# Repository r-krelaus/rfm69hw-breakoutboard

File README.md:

# rfm69hw-breakoutboard
KiCAD files for a SMD breakout board for the HopeRF transceiver module RFM69H/RFM69HW.
Needed this for a project to connect the 3.3 V RF module to 5 V Arduino.
Tested it and it works well.

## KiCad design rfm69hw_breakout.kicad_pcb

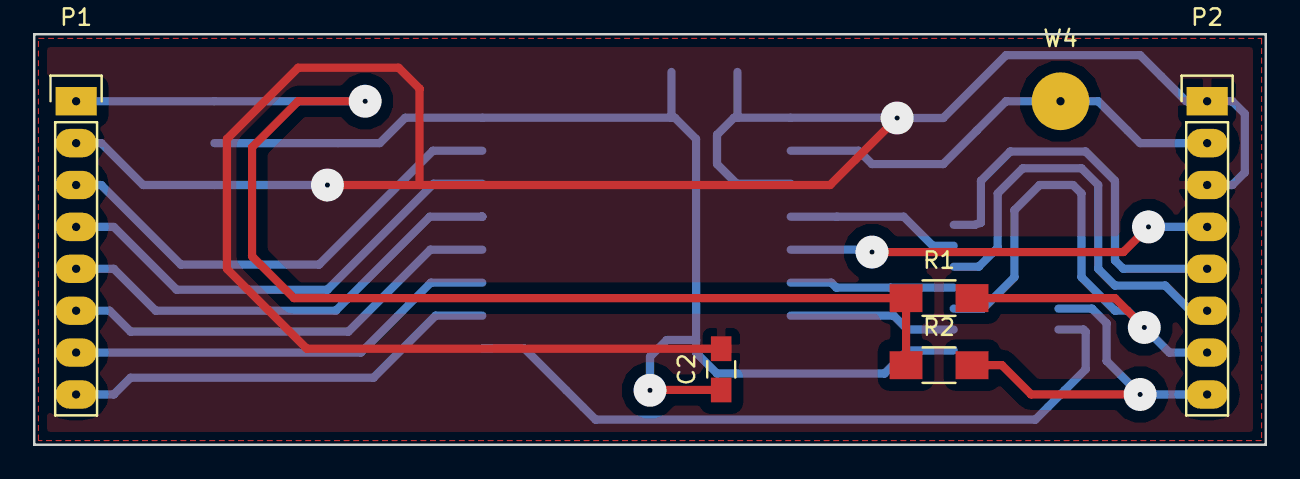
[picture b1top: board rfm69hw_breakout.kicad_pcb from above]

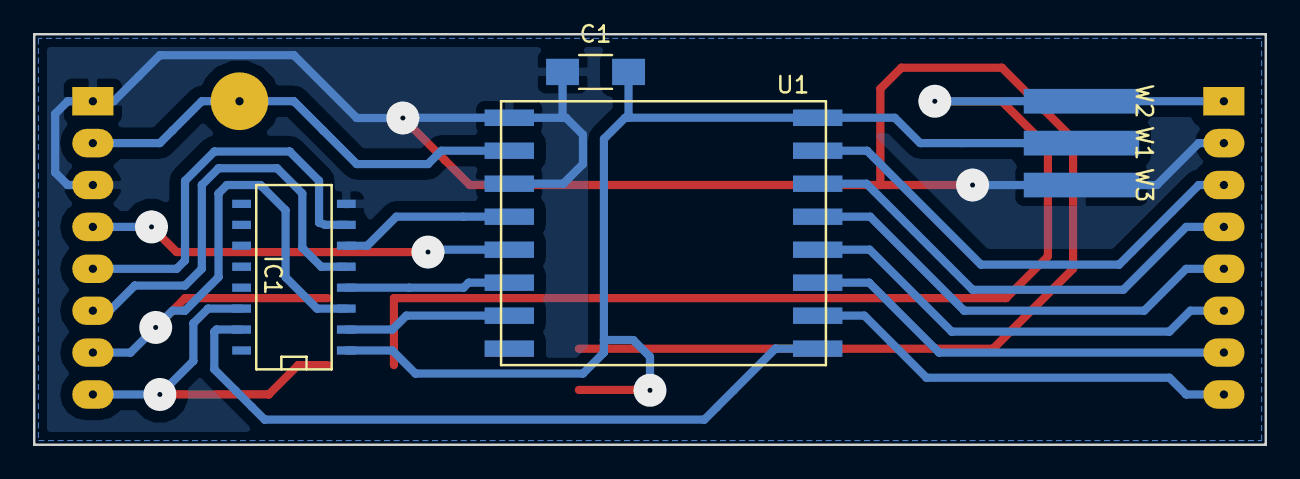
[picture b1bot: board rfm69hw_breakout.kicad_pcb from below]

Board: 2 copper layers, 74.7 x 24.9 mm, 12 parts (6 on the bottom side), 19 nets.

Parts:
C1: 10uF; C_1206_HandSoldering
C2: 0.1uF; C_0805_HandSoldering
IC1: 74HC4050; SO-16-N
P1, P2: CONN_01X08; Pin_Header_Straight_1x08
R1, R2: 100k; R_1206_HandSoldering
U1: RFM69; RFM69HW
W1, W2, W3: TEST_1P; SolderWirePad_single_SMD_5x10mm
W4: TEST_1P; SolderWirePad_single_1-2mmDrill

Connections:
+3V3: C1.2, C2.1, IC1.1, U1.8, W1.1
+5V: P1.1, R1.1, R2.1, W2.1
/CS_5V: IC1.3, P2.7, R1.2
/MISO_3V: P2.4, U1.13
/MOSI_5V: IC1.5, P2.6
/RST_5V: IC1.14, P2.8, R2.2
/SCK_5V: IC1.7, P2.5
GND: C1.1, C2.2, IC1.8, P1.2, P2.1, P2.3, U1.9, U1.11, W3.1
unnamed: IC1.2, U1.15
unnamed: IC1.4, U1.14
unnamed: IC1.6, U1.12
unnamed: IC1.15, U1.1
unnamed: P1.3, U1.7
unnamed: P1.4, U1.6
unnamed: P1.5, U1.5
unnamed: P1.6, U1.4
unnamed: P1.7, U1.3
unnamed: P1.8, U1.2
unnamed: P2.2, U1.10, W4.1
